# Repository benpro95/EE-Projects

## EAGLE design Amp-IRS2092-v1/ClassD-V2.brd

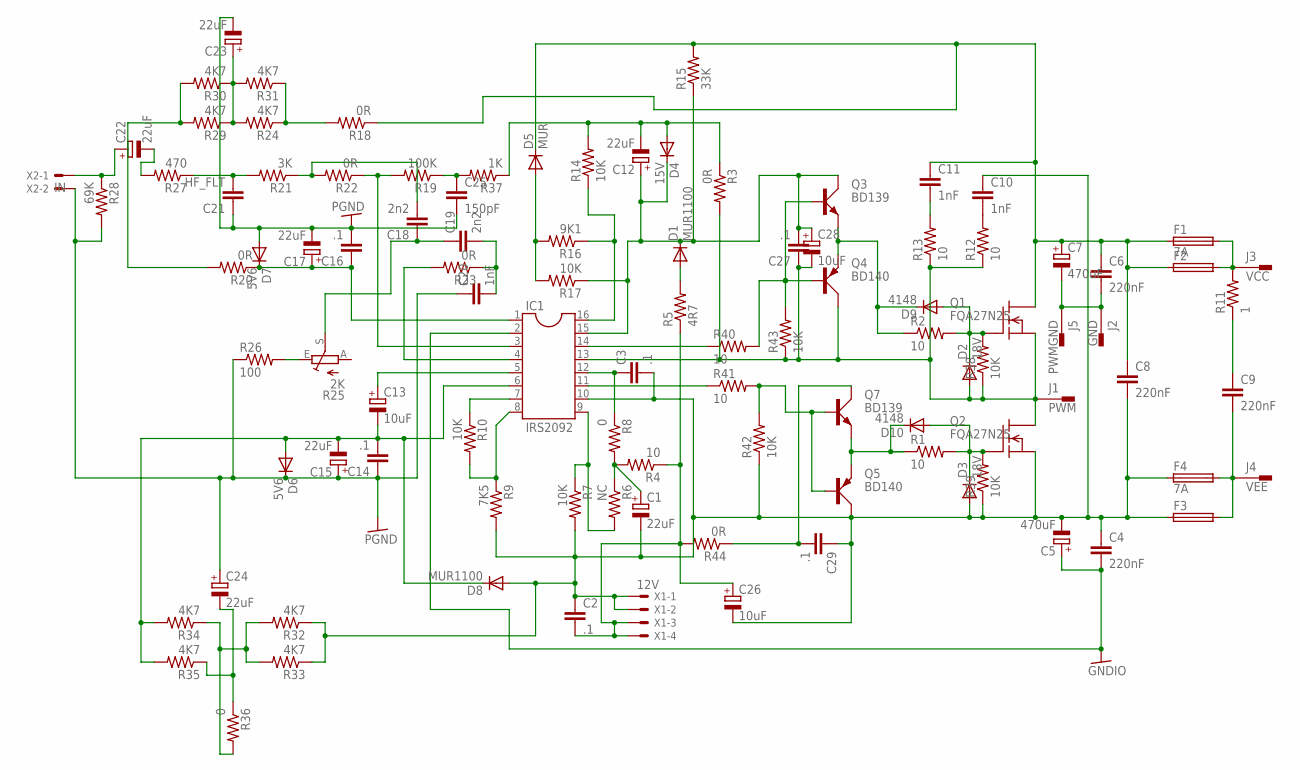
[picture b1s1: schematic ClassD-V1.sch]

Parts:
C1, C12, C15, C17, C22, C23, C24: 22uF; E5-10,5
C2, C3, C14, C16, C27, C29: .1; C1210K
C4, C6, C8, C9: 220nF; C22.5B11
C5, C7: 470uF; E7,5-16
C10, C11, C20: 1nF; C5B3.5
C13, C26, C28: 10uF; E3,5-8
C18, C19: 2n2; C5B3.5
C21: HF_FLT; C5B3.5
C25: 150pF; C5B3.5
D1, D8: MUR1100; DO41-10
D2, D3: 18V; DO35-10
D4: 15V; DO35-7
D5: MUR; DO35-10
D6: 5V6; DO35-10
D7: 5V6; DO35-7
D9, D10: 4148; DO35-10
F1, F4: 7A; KS9V
F2, F3: KS9V
IC1: IRS2092; DIL16
J1: PWM; F061.040
J2: GND; F061.040
J3: VCC; F061.040
J4: VEE; F061.040
J5: PWMGND; F061.040
Q1, Q2: FQA27N25; TOP3
Q3, Q7: BD139; TO126AV
Q4, Q5: BD140; TO126AV
R1, R2, R4, R40: 10; 0207/10
R3: 0R; 0207/12
R5: 4R7; 0207/10
R6: NC; 0207/10
R7, R10, R14, R17, R38, R39, R42, R43: 10K; 0207/10
R8, R36: 0; 0207/10
R9: 7K5; 0207/10
R11: 1; 0207/10
R12, R13: 10; 0309/12
R15: 33K; 0207/10
R16: 9K1; 0207/10
R18, R20, R22, R23: 0R; 0207/10
R19: 100K; 0207/10
R21: 3K; 0207/10
R24, R29, R30, R31, R32, R33, R34, R35: 4K7; 0617/22
R25: 2K; CT6
R26: 100; 0207/10
R27: 470; 0207/10
R28: 69K; 0207/10
R37: 1K; 0207/10
R41: 10; 0207/12
R44: 0R; 0204/7
X1: 12V; 22-23-2041
X2: IN; 22-23-2021

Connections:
COM: C1.-, C2.1, C3.2, C4.1, C5.-, C8.2, C10.1, C26.-, C29.1, D3.A, D8.A, F3.1, F4.1, IC1.10, Q2.3 (S), Q5.C, R7.2, R9.2, R32.1, R33.1, R39.1, R42.1, X1.1, X1.2
unnamed: D2.C, D9.A, Q1.1 (G), R2.2, R38.2
unnamed: D3.C, D10.A, Q2.1 (G), R1.2, R39.2
unnamed: IC1.8, R9.1, R10.2
unnamed: C6.1, C7.+, C8.1, C11.1, D5.C, F1.1, F2.1, Q1.2 (D), R15.2, R18.1
unnamed: IC1.14, R40.1
unnamed: IC1.11, R41.1
unnamed: D1.A, R5.2
unnamed: C9.2, F3.2, F4.2, J4.A1, J4.A2
unnamed: C3.1, IC1.12, R8.1
unnamed: C12.+, C27.2, C28.+, D1.C, D4.C, IC1.15, Q3.C, R15.1, R17.1
unnamed: IC1.9, R6.2, R7.1
unnamed: C1.+, R4.2, R6.1, R8.2
unnamed: C9.1, R11.1
unnamed: C11.2, R13.2
unnamed: D9.C, Q3.E, Q4.E, R2.1
unnamed: R25.E, R26.2
unnamed: C2.2, C26.+, R4.1, R5.1, R44.2, X1.3, X1.4
unnamed: IC1.7, R10.1
unnamed: F1.2, F2.2, J3.A1, J3.A2, R11.2
unnamed: C10.2, R12.2
unnamed: IC1.16, R14.1, R16.1
unnamed: D5.A, R16.2, R17.2
unnamed: C13.+, IC1.5
unnamed: C25.1, R19.1, R37.2
unnamed: IC1.3, R19.2, R22.1
unnamed: C18.1, C19.1, R25.S
unnamed: C19.2, C20.2, R23.1
unnamed: C18.2, R21.1, R22.2
unnamed: IC1.4, R23.2
unnamed: R18.2, R24.1, R31.1
unnamed: C21.2, R21.2, R27.1
unnamed: C22.-, R27.2
unnamed: C22.+, R28.1, X2.1
unnamed: C24.-, R35.1, R36.1
unnamed: C23.+, R24.2, R29.1, R30.1, R31.2
unnamed: R20.2, R29.2, R30.2
unnamed: R32.2, R33.2, R34.1, R36.2
unnamed: C13.-, C14.2, C15.-, D6.A, D8.C, IC1.6, R34.2, R35.2
unnamed: C12.-, D4.A, R3.1, R14.2, R37.1
unnamed: C27.1, C28.-, D2.A, IC1.13, J1.A1, J1.A2, Q1.3 (S), Q2.2 (D), Q4.C, R3.2, R12.1, R13.1, R38.1, R43.1
unnamed: Q5.B, Q7.B, R41.2, R42.2
unnamed: Q3.B, Q4.B, R40.2, R43.2
unnamed: C29.2, Q7.C, R44.1
unnamed: D10.C, Q5.E, Q7.E, R1.1
PGND: C4.2, C5.+, C6.2, C7.-, C14.1, C15.+, C16.2, C17.-, C20.1, C21.1, C23.-, C24.+, C25.2, D6.C, D7.A, IC1.2, J2.A1, J2.A2, J5.A1, J5.A2, R26.1, R28.2, X2.2
PGND1: C16.1, C17.+, D7.C, IC1.1, R20.1

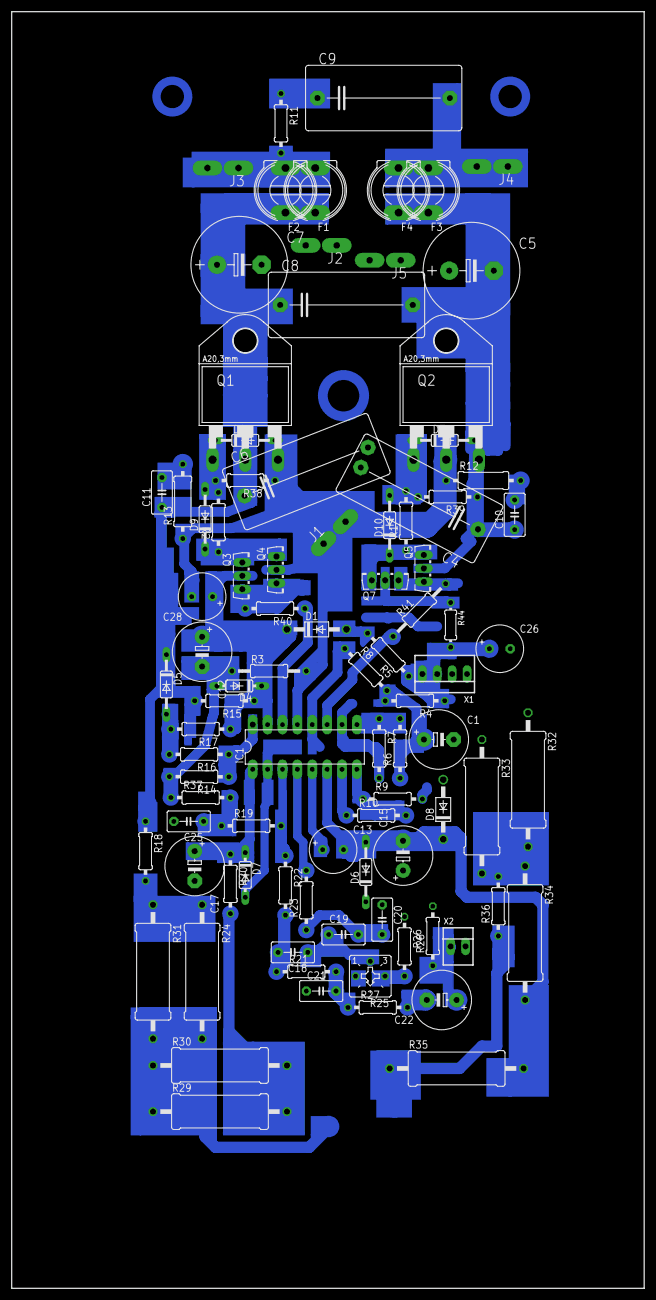
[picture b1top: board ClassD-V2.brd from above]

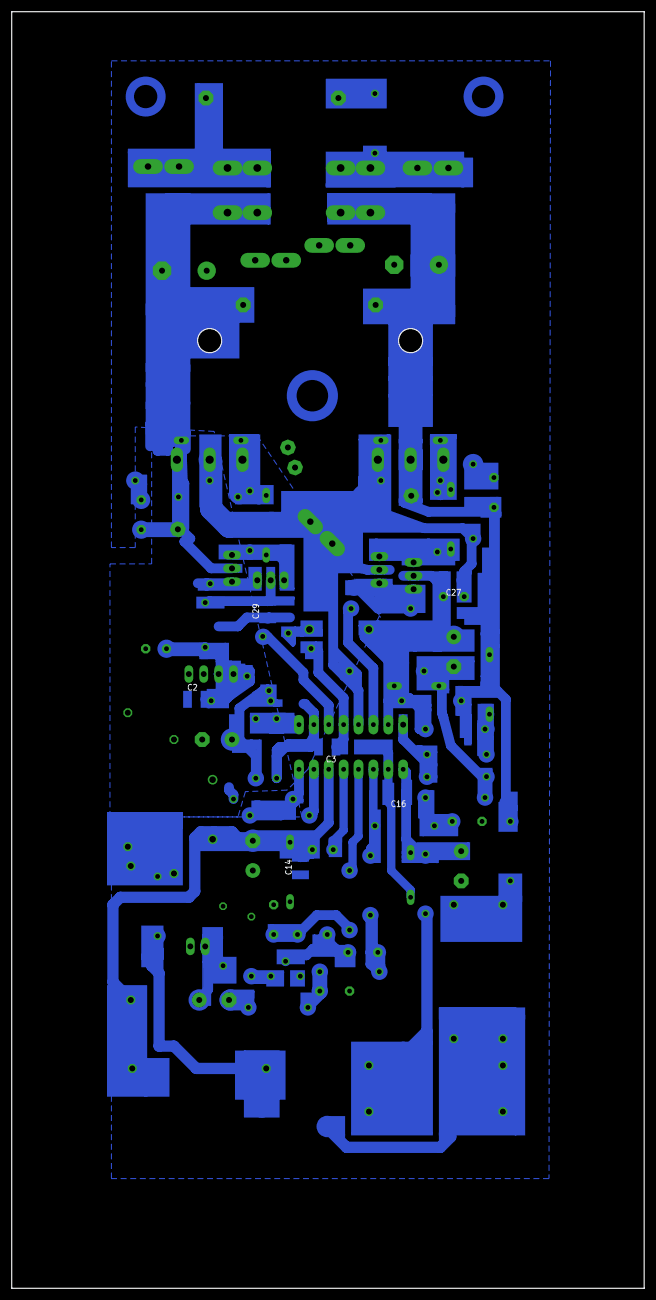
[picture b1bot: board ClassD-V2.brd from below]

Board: 2 copper layers, 107.9 x 217.9 mm, 97 parts (6 on the bottom side), 47 nets.

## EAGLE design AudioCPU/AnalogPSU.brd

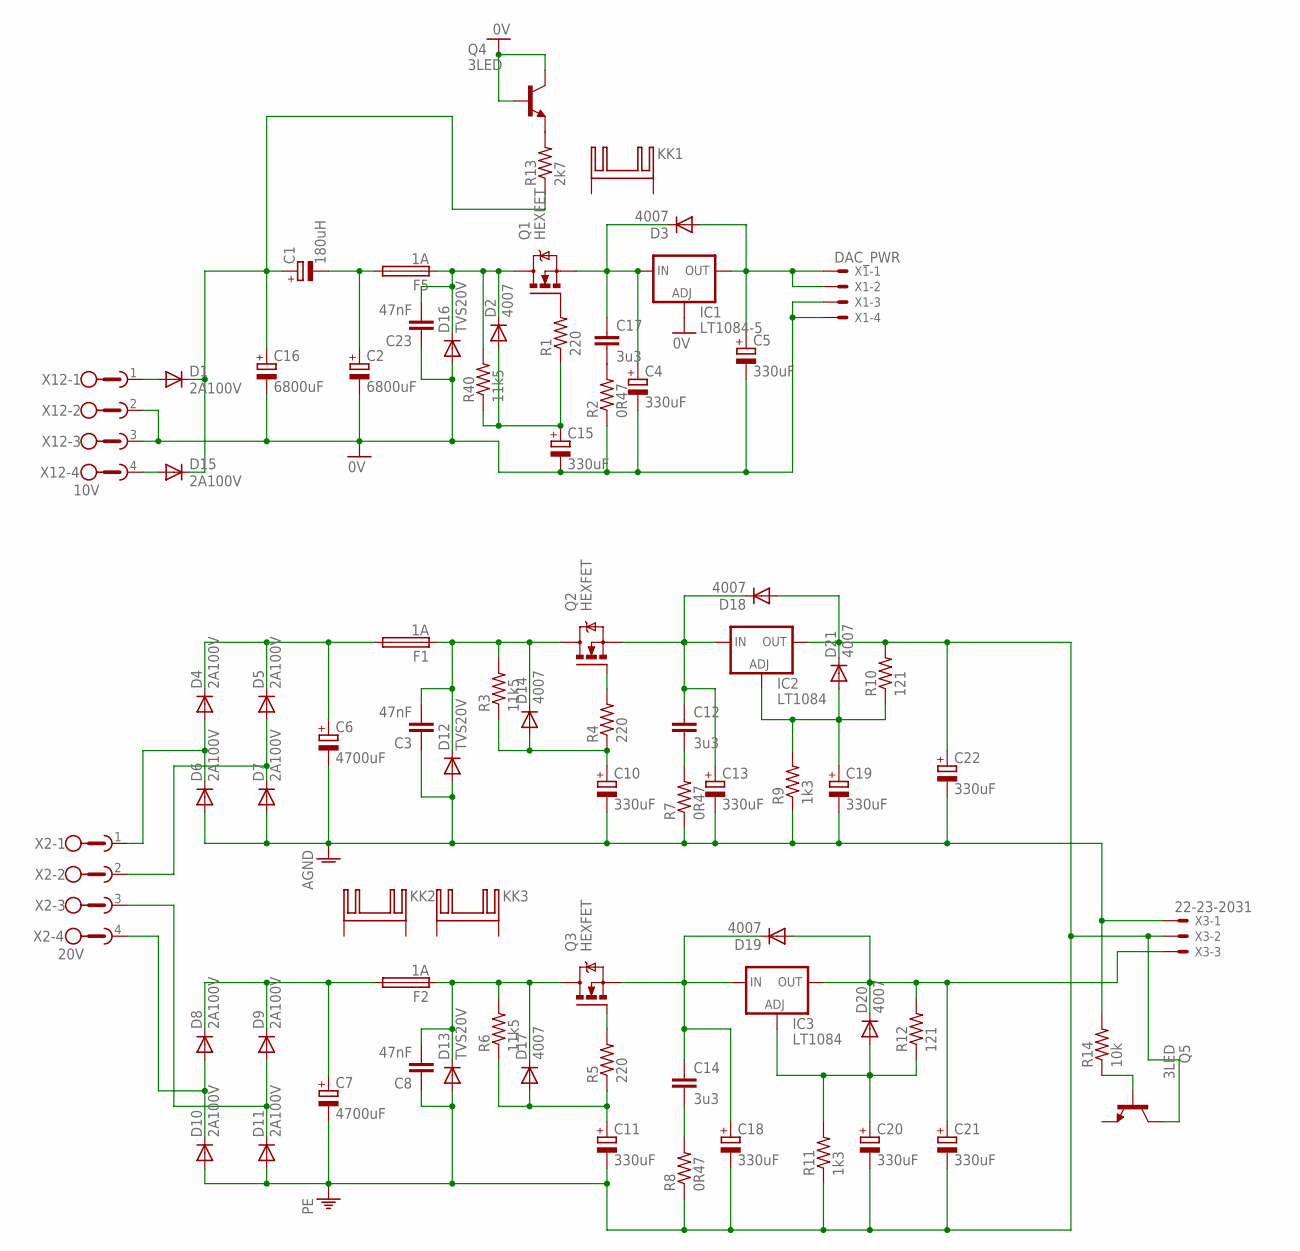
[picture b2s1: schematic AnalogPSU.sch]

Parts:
C1: 180uH; B45181C
C2, C16: 6800uF; EB20D
C3, C8, C23: 47nF; C050-075X075
C4, C5, C10, C11, C13, C15, C18, C19, C20, C21, C22: 330uF; E3,5-10
C6, C7: 4700uF; EB20D
C12, C14, C17: 3u3; C27.5B13
D1, D4, D5, D6, D7, D8, D9, D10, D11, D15: 2A100V; DO41-10
D2, D3, D14, D17: 4007; DO35-10
D12, D13, D16: TVS20V; SOD57-10
D18, D19, D20, D21: 4007; DO35-7
F1, F2, F5: 1A; 19560
IC1: LT1084-5; 317TS
IC2, IC3: LT1084; 317TS
KK1, KK2, KK3: SK104-PAD
Q1, Q2, Q3: HEXFET; TO220BV
Q4, Q5: 3LED; TO92-EBC
R1, R4, R5: 220; 0309/10
R2, R7, R8: 0R47; 0617V
R3, R6, R40: 11k5; 0309/10
R9, R11: 1k3; 0309/10
R10, R12: 121; 0309/10
R13: 2k7; 0309/12
R14: 10k; 0309/10
X1: DAC_PWR; 22-23-2041
X2: 20V; GMSTBA4
X3: 22-23-2031
X12: 10V; GMSTBA4

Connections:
0V: C2.-, C4.-, C5.-, C15.-, C16.-, C23.1, D16.A, IC1.1 (ADJ), Q4.B, Q4.C, R2.1, X1.3, X1.4, X12.2, X12.3
AGND: C3.1, C6.-, C10.-, C13.-, C19.-, C22.-, D6.A, D7.A, D12.A, R7.1, R9.1, R14.2, X3.1
unnamed: C17.2, R2.2
unnamed: D15.A, X12.4
unnamed: D1.A, X12.1
unnamed: C1.+, C16.+, D1.C, D15.C, R13.1
unnamed: C1.-, C2.+, F5.2
unnamed: C23.2, D2.C, D16.C, F5.1, Q1.D, R40.2
unnamed: C8.2, D13.C, D17.C, F2.1, Q3.D, R6.2
unnamed: C5.+, D3.A, IC1.2 (OUT), X1.1, X1.2
unnamed: C4.+, C17.1, D3.C, IC1.3 (IN), Q1.S
unnamed: C15.+, D2.A, R1.1, R40.1
unnamed: Q1.G, R1.2
unnamed: C6.+, D4.C, D5.C, F1.2
unnamed: C7.+, D8.C, D9.C, F2.2
unnamed: C3.2, D12.C, D14.C, F1.1, Q2.D, R3.2
unnamed: D8.A, D10.C, X2.4
unnamed: D9.A, D11.C, X2.3
unnamed: D4.A, D6.C, X2.1
unnamed: D5.A, D7.C, X2.2
unnamed: Q2.G, R4.2
unnamed: C10.+, D14.A, R3.1, R4.1
unnamed: C11.+, D17.A, R5.1, R6.1
unnamed: Q3.G, R5.2
unnamed: C14.1, C18.+, D19.C, IC3.3 (IN), Q3.S
unnamed: C14.2, R8.2
unnamed: C21.+, D19.A, D20.C, IC3.2 (OUT), R12.2, X3.3
unnamed: Q4.E, R13.2
unnamed: C20.+, D20.A, IC3.1 (ADJ), R11.2, R12.1
unnamed: Q5.B, R14.1
unnamed: C19.+, D21.A, IC2.1 (ADJ), R9.2, R10.1
unnamed: C12.1, C13.+, D18.C, IC2.3 (IN), Q2.S
unnamed: C12.2, R7.2
PE: C7.-, C8.1, C11.-, C18.-, C20.-, C21.-, C22.+, D10.A, D11.A, D13.A, D18.A, D21.C, IC2.2 (OUT), Q5.C, R8.1, R10.2, R11.1, X3.2

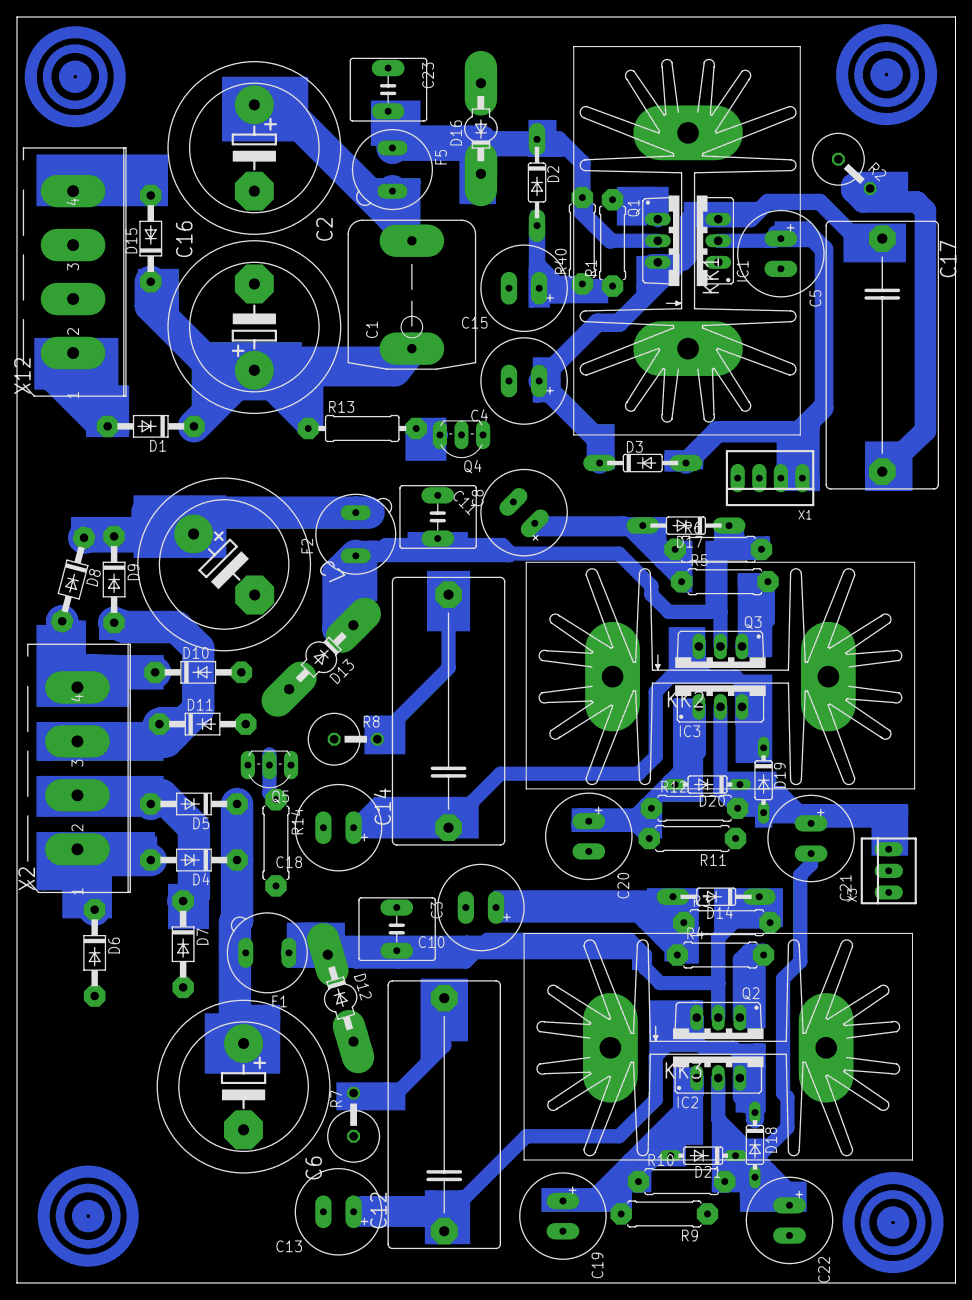
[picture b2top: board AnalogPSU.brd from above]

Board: 2 copper layers, 110.5 x 149.0 mm, 76 parts (0 on the bottom side), 34 nets.

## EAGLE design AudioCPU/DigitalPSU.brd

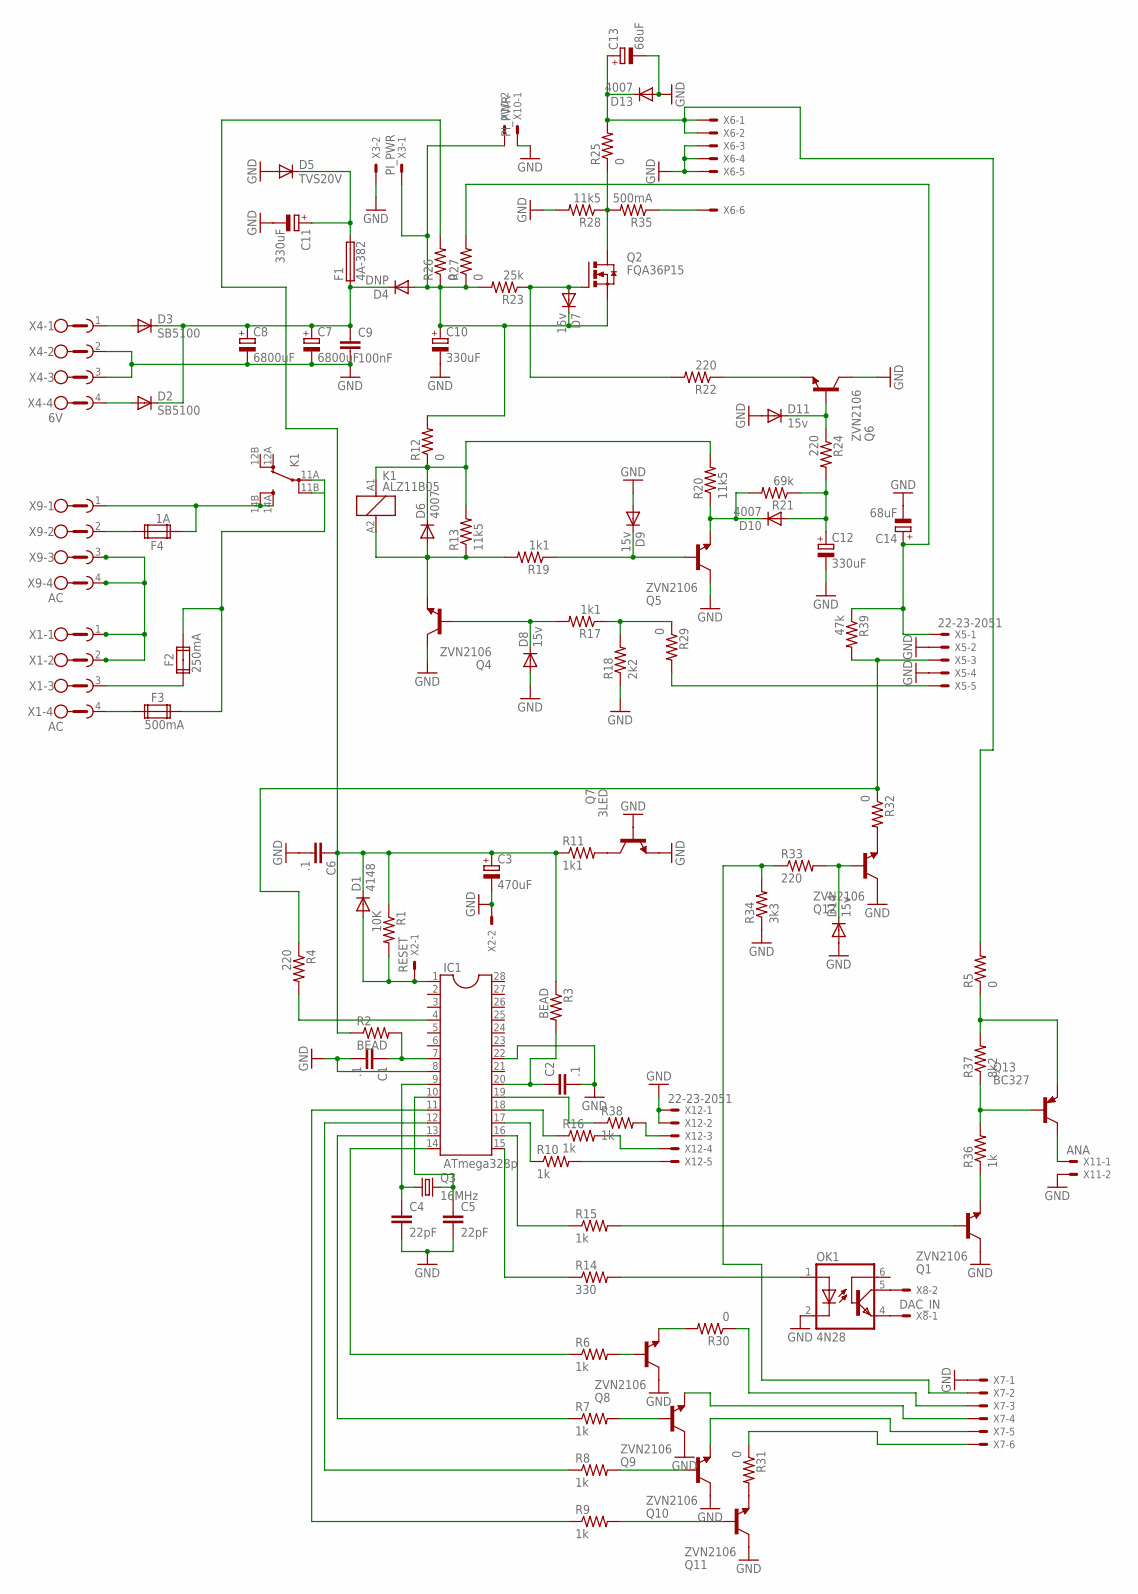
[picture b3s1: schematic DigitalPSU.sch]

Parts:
C1, C2, C6: .1; C1210K
C3: 470uF; E3,5-10
C4, C5: 22pF; C1210K
C7, C8: 6800uF; EB20D
C9: 100nF; C10B6
C10, C11, C12: 330uF; E3,5-10
C13, C14: 68uF; E3,5-10
D1: 4148; DO35-7
D2, D3: SB5100; SOD57-10
D4: DNP; DO41-10
D5: TVS20V; SOD57-10
D6, D13: 4007; DO41-10
D7: 15v; DO35-10
D8, D9, D11, D14: 15v; DO35-7
D10: 4007; DO35-10
F1: 4A-382; 19560
F2: 250mA; FUSE1
F3: 500mA; FUSE1
F4: 1A; FUSE1
IC1: ATmega328p; DIL28-3
K1: ALZ11B05; RT-C/O16A5
OK1: 4N28; DIL06
Q1, Q4, Q5, Q6, Q8, Q9, Q10, Q11, Q12: ZVN2106; TO92-EBC
Q2: FQA36P15; TO247BV
Q3: 16MHz; HC49/S
Q7: 3LED; TO92-EBC
Q13: BC327; TO92-EBC
R1: 10K; 0309/10
R2: BEAD; 0309/10
R3: BEAD; 0309/12
R4, R33: 220; 0309/12
R5, R25, R26, R27, R31, R32: 0; 0309/12
R6, R7, R8, R9, R10, R15, R16, R36, R38: 1k; R1210
R11, R17, R19: 1k1; 0309/10
R12, R29, R30: 0; 0309/10
R13, R20: 11k5; 0309/10
R14: 330; 0309/10
R18: 2k2; 0309/10
R21: 69k; 0309/10
R22, R24: 220; 0309/10
R23: 25k; 0309/10
R28: 11k5; 0204/5
R34: 3k3; 0309/12
R35: 500mA; 0204/5
R37: 8k2; R1210
R39: 47k; 0309/10
X1, X9: AC; GMSTBA4
X2: RESET; 22-23-2021
X3, X10: PI_PWR; 22-23-2021
X4: 6V; GMSTBA4
X5, X12: 22-23-2051
X6, X7: 22-23-2061
X8: DAC_IN; 22-23-2021
X11: ANA; 22-23-2021

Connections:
GND: C1.2, C2.2, C3.-, C4.2, C5.2, C6.2, C7.-, C8.-, C9.2, C10.-, C11.-, C12.-, C13.-, C14.-, D5.A, D8.A, D9.A, D11.A, D13.A, D14.A, IC1.8, IC1.22, OK1.2 (C), Q1.C, Q4.C, Q5.C, Q6.C, Q7.B, Q7.E, Q8.C, Q9.C, Q10.C, Q11.C, Q12.C, R18.1, R28.2, R34.1, X2.2, X3.2, X4.2, X4.3, X5.2, X5.4, X6.3, X6.4, X6.5, X7.1, X10.1, X11.2, X12.1, X12.2
unnamed: IC1.14, R6.1
unnamed: D1.A, IC1.1, R1.2, X2.1
unnamed: IC1.4, R4.2
unnamed: C2.1, IC1.20, R3.2
unnamed: R4.1, R32.1, R39.2, X5.3
unnamed: IC1.13, R7.1
unnamed: IC1.12, R8.1
unnamed: C11.+, D5.C, F1.2
unnamed: IC1.11, R9.1
unnamed: IC1.18, R16.1
unnamed: C10.+, D4.A, D7.C, Q2.S, R12.2, R23.2, R26.1, R27.1, X3.1, X10.2
unnamed: C4.1, IC1.9, Q3.1
unnamed: C5.1, IC1.10, Q3.2
unnamed: X1.1, X1.2, X9.3, X9.4
unnamed: F2.1A, X1.3
unnamed: F3.1A, X1.4
unnamed: IC1.15, R14.1
unnamed: IC1.16, R15.1
unnamed: IC1.17, R10.1
unnamed: F4.2A, X9.2
unnamed: Q7.C, R11.2
unnamed: F4.1A, K1.14A (SA), K1.14B (SB), X9.1
unnamed: F2.2A, F3.2A, K1.11A (PA), K1.11B (PB)
unnamed: C3.+, C6.1, D1.C, R1.1, R2.1, R3.1, R11.1, R26.2
unnamed: D3.A, X4.1
unnamed: D2.A, X4.4
unnamed: IC1.19, R38.1
unnamed: C7.+, C8.+, C9.1, D2.C, D3.C, D4.C, F1.1
unnamed: D6.C, K1.A1 (1), R12.1, R13.2, R20.2
unnamed: D6.A, K1.A2 (2), Q4.E, R13.1, R19.2
unnamed: D7.A, Q2.G, R22.2, R23.1
unnamed: C1.1, IC1.7, R2.2
unnamed: D8.C, Q4.B, R17.2
unnamed: R29.2, X5.5
unnamed: D9.C, Q5.B, R19.1
unnamed: D10.C, Q5.E, R20.1, R21.2
unnamed: C12.+, D10.A, R21.1, R24.2
unnamed: R38.2, X12.3
unnamed: Q6.E, R22.1
unnamed: D11.C, Q6.B, R24.1
unnamed: Q2.D, R25.1, R28.1, R35.2
unnamed: R17.1, R18.2, R29.1
unnamed: C14.+, R27.2, R39.1, X5.1
unnamed: Q8.B, R6.2
unnamed: Q9.B, R7.2
unnamed: Q10.B, R8.2
unnamed: Q11.B, R9.2
unnamed: Q8.E, R30.2
unnamed: Q11.E, R31.2
unnamed: Q12.E, R32.2
unnamed: D14.C, Q12.B, R33.2
unnamed: R33.1, R34.2, X7.2
unnamed: Q10.E, X7.5
unnamed: Q9.E, X7.4
unnamed: R31.1, X7.6
unnamed: R35.1, X6.6
unnamed: R30.1, X7.3
unnamed: C13.+, D13.C, R5.2, R25.2, X6.1, X6.2
unnamed: OK1.1 (A), R14.2
unnamed: OK1.4 (EMI), X8.1
unnamed: OK1.5 (COL), X8.2
unnamed: Q1.B, R15.2
unnamed: Q1.E, R36.1
unnamed: Q13.B, R36.2, R37.1
unnamed: Q13.E, R5.1, R37.2
unnamed: R16.2, X12.4
unnamed: Q13.C, X11.1
unnamed: R10.2, X12.5

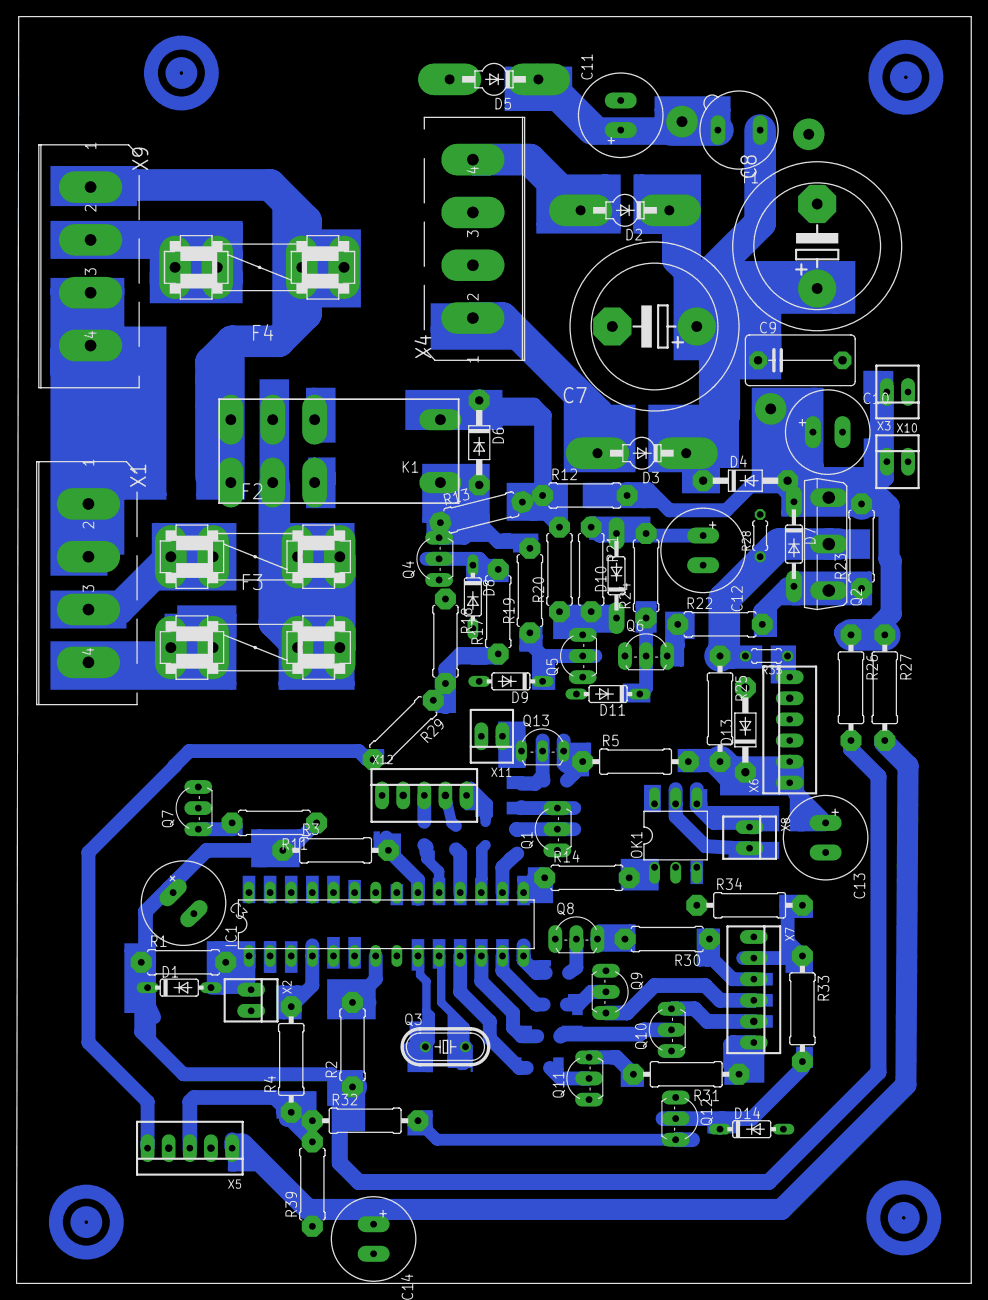
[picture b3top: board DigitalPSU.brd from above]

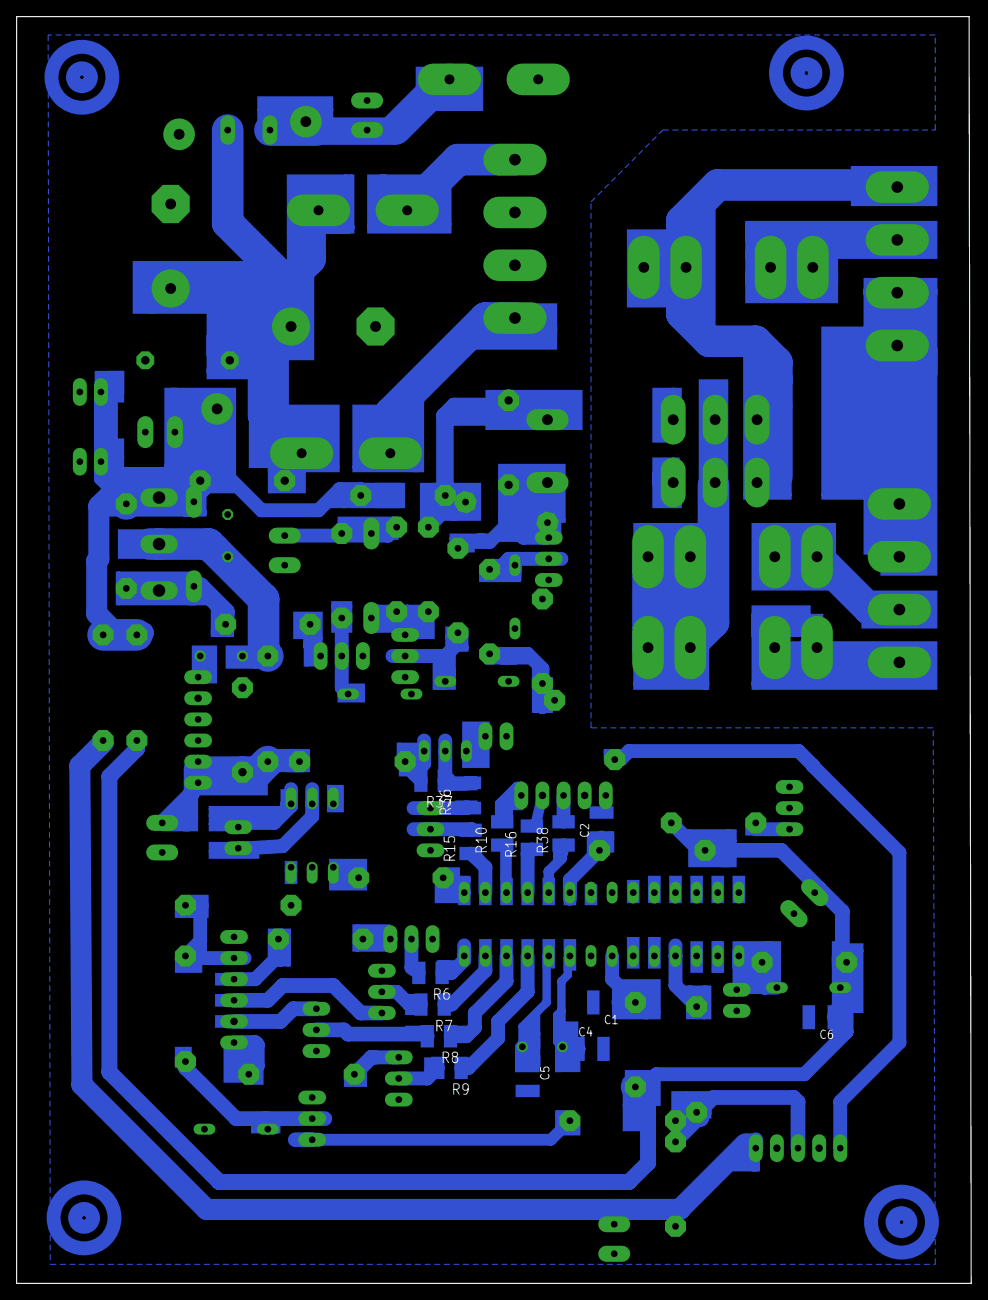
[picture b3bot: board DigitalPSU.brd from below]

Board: 2 copper layers, 114.8 x 152.3 mm, 98 parts (15 on the bottom side), 69 nets.

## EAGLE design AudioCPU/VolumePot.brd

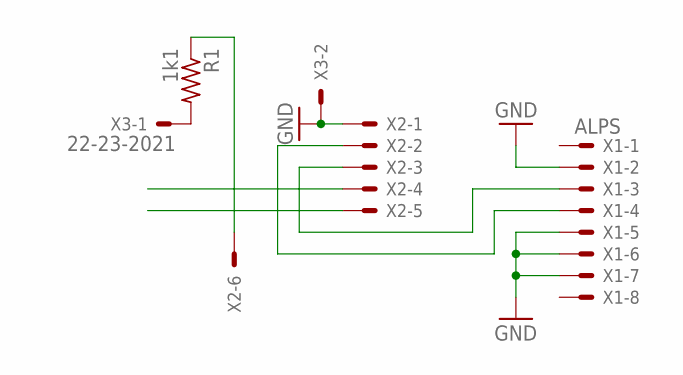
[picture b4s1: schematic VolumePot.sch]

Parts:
R1: 1k1; 0309/12
X1: ALPS; 22-23-2081
X2: 22-23-2061
X3: 22-23-2021

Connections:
CCW: X2.5
CW: X2.4
GND: X1.2, X1.5, X1.6, X1.7, X2.1, X3.2
unnamed: R1.2, X3.1
unnamed: X1.3, X2.3
unnamed: R1.1, X2.6
unnamed: X1.4, X2.2

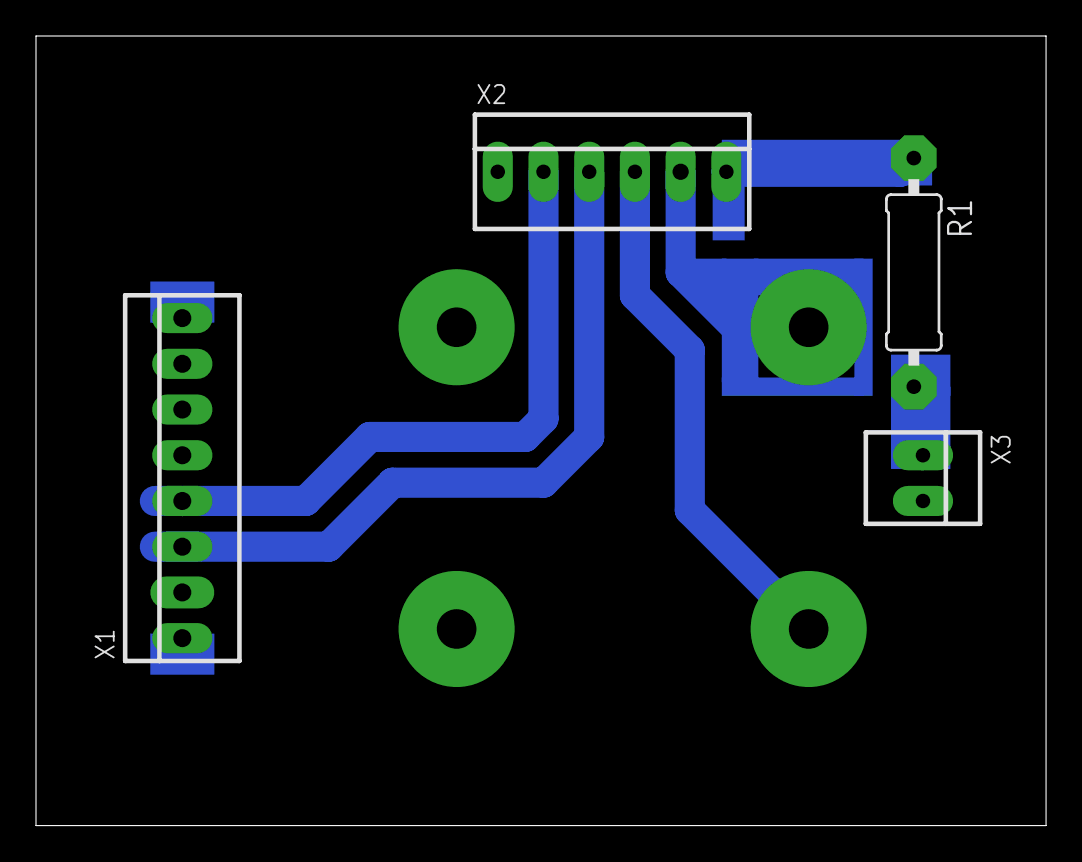
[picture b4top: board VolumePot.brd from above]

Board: 2 copper layers, 56.1 x 43.9 mm, 4 parts (0 on the bottom side), 5 nets.
